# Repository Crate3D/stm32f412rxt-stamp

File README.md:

# stm32f412rxt-stamp
Small STM32F412RxT based board for prototyping

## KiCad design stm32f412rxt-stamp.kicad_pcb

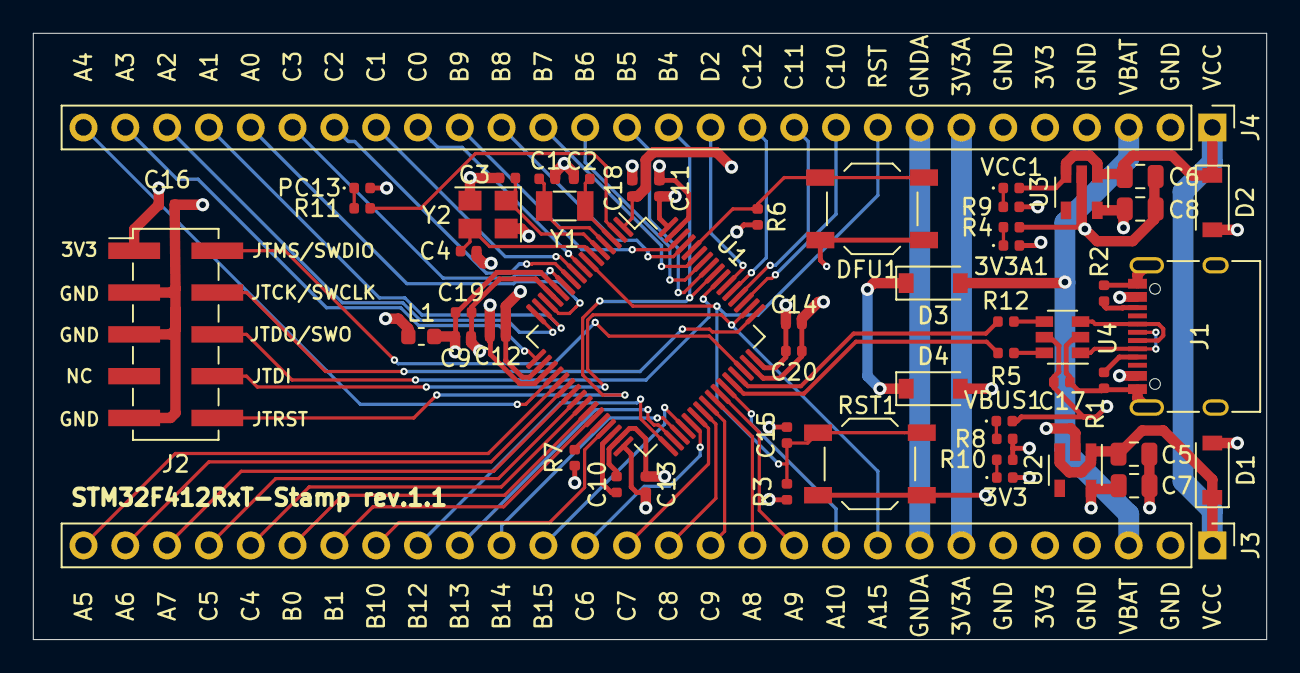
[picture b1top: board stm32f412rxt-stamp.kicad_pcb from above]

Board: 4 copper layers, 74.9 x 36.8 mm, 54 parts (0 on the bottom side), 72 nets.

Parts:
3V3: 3V3; LED_0402_1005Metric
3V3A1: 3V3A; LED_0402_1005Metric
C1, C2, C3, C4: 10p; C_0402_1005Metric
C5, C6, C7, C8: 1uF; C_0805_2012Metric
C9: 1uF; C_0402_1005Metric
C10: 2.2uF; C_0402_1005Metric
C11, C12, C13, C15, C16, C17, C18, C20: 100nF; C_0402_1005Metric
C14: 4.7uF; C_0402_1005Metric
C19: 10nF; C_0402_1005Metric
D1, D2, D3, D4: MBR120VLSFT1G; D_SOD-123
DFU1: XKB Enterprise TS-1187A-C-D-B; SW_SPST_TL3342
J1: USB_C_Receptacle_USB2.0; USB_C_Receptacle_XKB_U262-16XN-4BVC11
J2: JTAG; PinHeader_2x05_P2.54mm_Vertical_SMD
J3, J4: Conn_01x28; PinHeader_1x28_P2.54mm_Vertical
L1: BLM18BB470SN1D; L_0603_1608Metric
PC13: PC13; LED_0402_1005Metric
R1, R2: 5.1k; R_0402_1005Metric
R3, R6, R7: 10k; R_0402_1005Metric
R4, R10, R11: 100R; R_0402_1005Metric
R5, R12: 22R; R_0402_1005Metric
R8, R9: 220R; R_0402_1005Metric
RST1: XKB Enterprise TS-1187A-C-D-B; SW_SPST_TL3342
U1: STM32F412RETx; LQFP-64_10x10mm_P0.5mm
U2, U3: AP2112K-3.3TRG1; SOT-23-5
U4: USBLC6-2SC6; SOT-23-6
VBUS1: VBUS; LED_0402_1005Metric
VCC1: VCC; LED_0402_1005Metric
Y1: 32.768kHz; Crystal_SMD_3215-2Pin_3.2x1.5mm
Y2: 16MHz; Crystal_SMD_3225-4Pin_3.2x2.5mm

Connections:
BOOT0: DFU1.1, R6.1, U1.60
BOOT1: R7.1, U1.28
JTCK-SWCLK: J2.4, U1.49
JTDO-SWO: J2.6, U1.55
JTMS-SWDIO: J2.2, U1.46
NRST: C15.1, J4.9, R3.1, RST1.2, U1.7
unnamed: 3V3.1, R10.2
unnamed: 3V3A1.1, R4.2
unnamed: J1.A5, R1.2
unnamed: J1.A6, J1.B6, U4.3
unnamed: J1.A7, J1.B7, U4.1
unnamed: J1.B5, R2.2
unnamed: PC13.1, R11.2
unnamed: R5.1, U4.6
unnamed: R8.2, VBUS1.1
unnamed: R9.2, VCC1.1
unnamed: R12.1, U4.4
PA0: J4.24, U1.14
PA1: J4.25, U1.15
PA2: J4.26, U1.16
PA3: J4.27, U1.17
PA4: J4.28, U1.20
PA5: J3.28, U1.21
PA6: J3.27, U1.22
PA7: J3.26, U1.23
PA8: J3.12, U1.41
PA9: J3.11, U1.42
PA10: J3.10, U1.43
PA15-JTDI: J2.8, J3.9, U1.50
PB0: J3.23, U1.26
PB1: J3.22, U1.27
PB4-JTRST: J2.10, J4.14, U1.56
PB5: J4.15, U1.57
PB6: J4.16, U1.58
PB7: J4.17, U1.59
PB8: J4.18, U1.61
PB9: J4.19, U1.62
PB10: J3.21, U1.29
PB12: J3.20, U1.33
PB13: J3.19, U1.34
PB14: J3.18, U1.35
PB15: J3.17, U1.36
PC0: J4.20, U1.8
PC1: J4.21, U1.9
PC2: J4.22, U1.10
PC3: J4.23, U1.11
PC4: J3.25, U1.24
PC5: J3.24, U1.25
PC6: J3.16, U1.37
PC7: J3.15, U1.38
PC8: J3.14, U1.39
PC9: J3.13, U1.40
PC10: J4.10, U1.51
PC11: J4.11, U1.52
PC12: J4.12, U1.53
PC13: R11.1, U1.2
PD2: J4.13, U1.54
USB_D+: R12.2, U1.45
USB_D-: R5.2, U1.44
VB: D3.2, J3.3, J4.3
VBAT: C18.2, D3.1, D4.1, U1.1
VBUS: C17.1, D1.2, D2.2, J1.A4, J1.A9, J1.B4, J1.B9, U4.5, VBUS1.2
VCAP: C10.1, U1.30
VCC: C5.1, C6.1, D1.1, D2.1, J3.1, J4.1, U2.1, U2.3, U3.1, U3.3, VCC1.2
VDD: 3V3.2, C7.1, C11.1, C12.1, C13.1, C14.1, C16.2, C20.1, D4.2, DFU1.2, J2.1, J3.5, J4.5, PC13.2, R3.2, U1.19, U1.32, U1.48, U1.64, U2.5
VDDA: 3V3A1.2, C8.1, C9.1, C19.1, J3.7, J4.7, U1.13, U3.5
VSS: C1.1, C2.1, C3.2, C4.2, C5.2, C7.2, C10.2, C11.2, C12.2, C13.2, C14.2, C15.2, C16.1, C17.2, C18.1, C20.2, J1.A1, J1.A12, J1.B1, J1.B12, J1.S1, J2.3, J2.5, J2.9, J3.2, J3.4, J3.6, J4.2, J4.4, J4.6, L1.1, R1.1, R2.1, R6.2, R7.2, R8.1, R9.1, R10.1, RST1.1, U1.18, U1.31, U1.47, U1.63, U2.2, U4.2, Y2.2, Y2.4
VSSA: C6.2, C8.2, C9.2, C19.2, J3.8, J4.8, L1.2, R4.1, U1.12, U3.2
osc32-in: C2.2, U1.3, Y1.2
osc32-out: C1.2, U1.4, Y1.1
osc-in: C3.1, U1.5, Y2.1
osc-out: C4.1, U1.6, Y2.3

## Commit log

2020-01-08 Rev.1 of STM32F412RxT Stamp board
2020-04-04 Update gitignore
2020-04-04 Fix RST button
2020-04-04 Drop *bak
2020-04-04 Fix usb esd supressor
2020-04-04 Fix usb =)
2020-04-04 rev is 1.1-dev
2020-04-04 Fix leds
2020-04-15 Fix gitignore
2020-04-15 New revision 1.1
2020-04-15 Fix sym-libs

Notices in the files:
stm32f412rxt-stamp.kicad_pcb:
Licensed under GPLv3
